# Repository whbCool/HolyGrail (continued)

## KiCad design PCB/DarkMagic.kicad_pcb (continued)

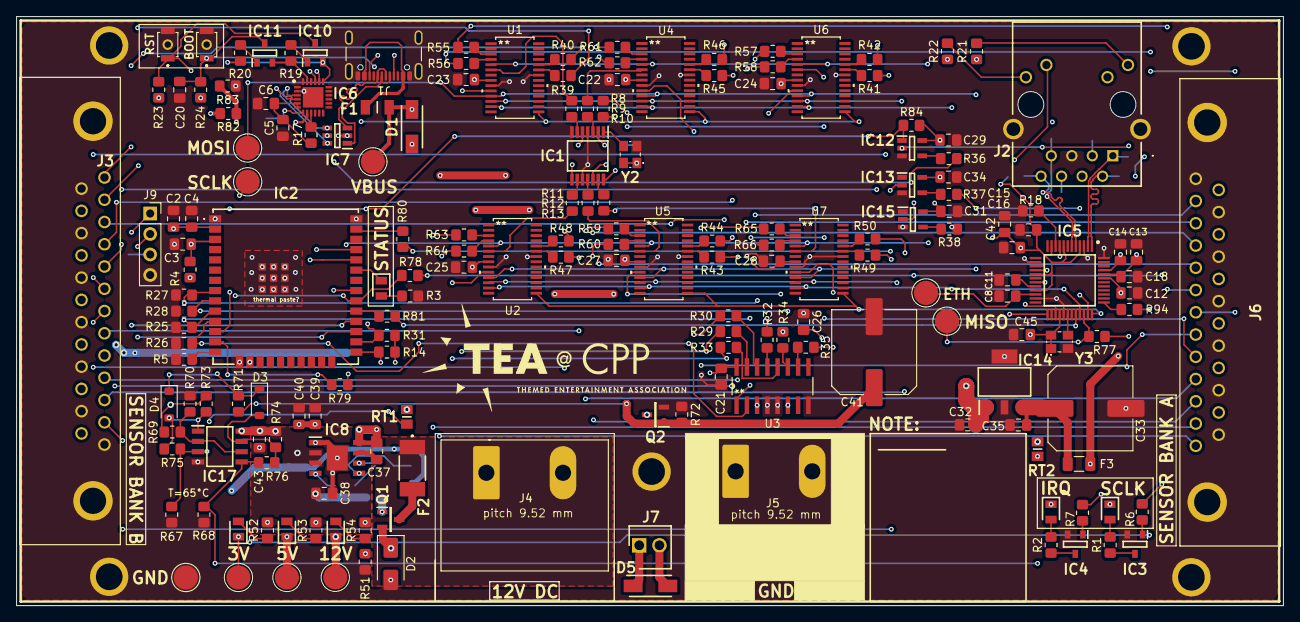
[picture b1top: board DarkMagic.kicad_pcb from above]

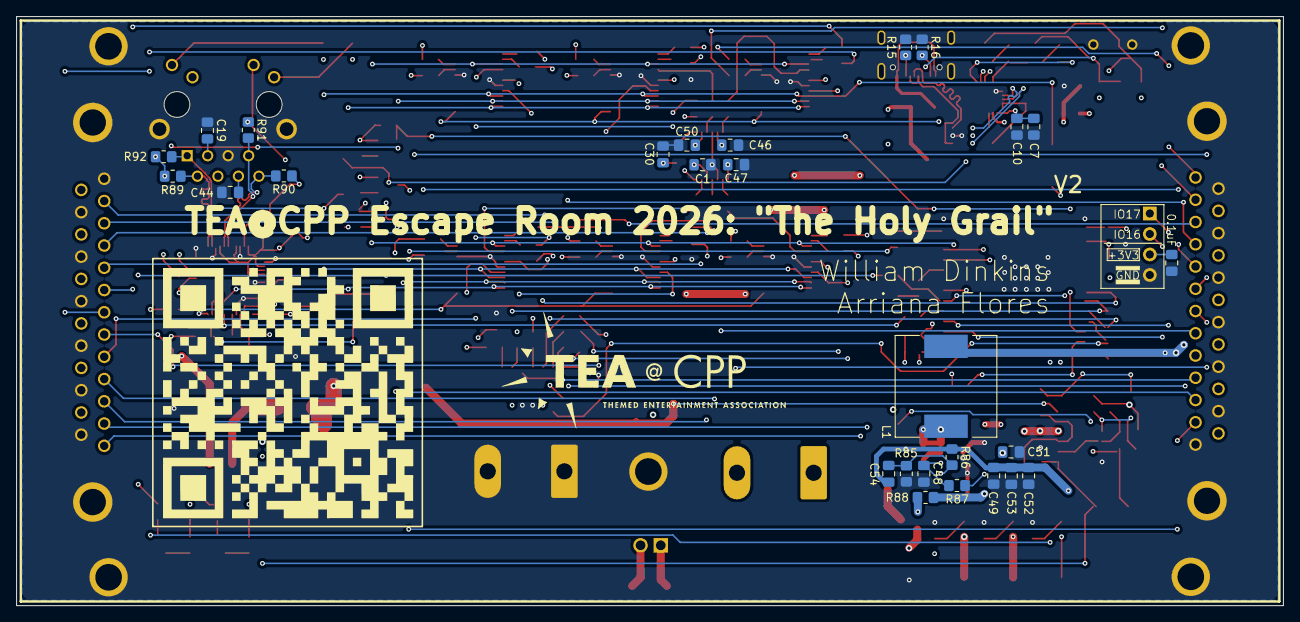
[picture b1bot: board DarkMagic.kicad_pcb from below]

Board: 6 copper layers, 157.0 x 73.0 mm, 212 parts (27 on the bottom side), 165 nets.

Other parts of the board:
C3, C4: 10uF; C_0805_2012Metric_Pad1.18x1.45mm_HandSolder
IC2: ESP32-WROOM-32UE-N16; ESP32WROOM32UEN16
IC3, IC4: MMBT3904-AQ; SOT95P240X120-3N
IRQ1: HSMN-C170; LEDC2012X90N
J9: Conn_01x04; PinSocket_1x04_P2.54mm_Vertical
R1, R2, R3: 330; R_0805_2012Metric_Pad1.20x1.40mm_HandSolder
R4, R5, R14: 10k; R_0805_2012Metric_Pad1.20x1.40mm_HandSolder
R6, R7: 4.7K; R_0805_2012Metric_Pad1.20x1.40mm_HandSolder
R8, R9, R10, R11, R12, R13: 33; R_0805_2012Metric_Pad1.20x1.40mm_HandSolder
SCLK1: HSMN-C170; LEDC2012X90N
STATUS1: HSMG-C170; LEDC2012X80N

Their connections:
/ESP_A0: IC2.10 (IO25); also elsewhere on the board
/ESP_A1: IC2.11 (IO26); also elsewhere on the board
/ESP_A2: IC2.8 (IO32); also elsewhere on the board
/ESP_E3: IC2.9 (IO33); also elsewhere on the board
/ESP_EN: C3.1, IC2.3 (EN), R4.1; also elsewhere on the board
/ESP_IO0: IC2.25 (IO0), R14.1; also elsewhere on the board
/ESP_IRQ: IC2.26 (IO4), R7.1; also elsewhere on the board
/ESP_MISO: IC2.31 (IO19); also elsewhere on the board
/ESP_MOSIT: IC2.37 (IO23); also elsewhere on the board
/ESP_RX0: IC2.34 (RXD0); also elsewhere on the board
/ESP_SCLK: R6.1; also elsewhere on the board
/ESP_SCLKT: IC2.30 (IO18); also elsewhere on the board
/ESP_SCSNT: IC2.29 (IO5); also elsewhere on the board
/ESP_TX0: IC2.35 (TXD0); also elsewhere on the board
/ESP_USRSTT: IC2.13 (IO14); also elsewhere on the board
/IO12: IC2.14 (IO12), R5.2
/IO16: IC2.27 (IO16), J9.2
/IO17: IC2.28 (IO17), J9.1
/IO21: IC2.33 (IO21), STATUS1.1 (K)
/IRQ_STAT: IC4.3 (C), R2.1
/OE: IC2.12 (IO27); also elsewhere on the board
/SCLK_STAT: IC3.3 (C), R1.1
/W5500_RST: IC2.16 (IO13); also elsewhere on the board
/XS1: R8.2; also elsewhere on the board
/XS1T: R8.1; also elsewhere on the board
/XS2: R9.2; also elsewhere on the board
/XS3: R10.2; also elsewhere on the board
/XS3T: R10.1; also elsewhere on the board
/XS4: R11.2; also elsewhere on the board
/XS4T: R11.1; also elsewhere on the board
/XS5: R12.2; also elsewhere on the board
/XS5T: R12.1; also elsewhere on the board
/XS6: R13.2; also elsewhere on the board
/XS6T: R13.1; also elsewhere on the board
unnamed: IC3.1 (B), R6.2
unnamed: IC4.1 (B), R7.2
unnamed: IRQ1.2 (A), R2.2
unnamed: R1.2, SCLK1.2 (A)
unnamed: R3.1, STATUS1.2 (A)

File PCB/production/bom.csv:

Designator,Footprint,Quantity,Value,LCSC Part #
12V1,LEDC2012X90N,1,HSMC-C170,
"3V1, STATUS1",LEDC2012X80N,2,HSMG-C170,
5V1,LEDC2012X90N,1,HSMA-C170,
"C1, C10, C12, C13, C14, C15, C16, C17, C18, C19, C2, C20, C21, C22, C23, C24, C25, C26, C27, C28, C29, C30, C31, C34, C35, C37, C42, C43, C44, C45, C46, C47, C50, C6, C8, C9",0805,36,0.1uF,
C11,0805,1,10nF,
"C3, C32, C38, C4",0805,4,10uF,
C33,C_Elec_10x10.2,1,33uF,
"C39, C40, C49, C52, C53",0805,5,22uF,
C41,C_Elec_10x10.2,1,47uF,
C48,0805,1,1uF,
"C5, C7",0805,2,4.7uF,
C51,0805,1,220nF,
C54,0805,1,39pF,
"D1, D5",DIOM5226X230N,2,B130-13-F,
D2,D_SMA,1,SMBJ26A,
"D3, D4",D_SOD-123,2,1N4148W,
F1,FUSC3216X74N,1,NANOSMDC050F_13.2-2,
F2,1812L010DR,1,1812L150_24MR,
IC1,SOP65P640X120-14N,1,5PB1106PGGI8,
"IC10, IC11, IC3, IC4",SOT95P240X120-3N,4,MMBT3904-AQ,
"IC12, IC13, IC15",SOT95P280X145-5N,3,SN74LVC1G125DBVT,
IC14,SOT230P700X180-4N,1,LM3940IMP-3.3_NOPB,
IC17,SOIC127P600X175-8N,1,LM393DR,
IC2,ESP32WROOM32UEN16,1,ESP32-WROOM-32UE-N16,
IC5,QFP50P900X900X160-48N,1,W5500,
IC6,QFN50P400X400X80-25N-D,1,CP2102N-A02-GQFN24,
IC7,SOT95P280X145-6N,1,USBLC6-2SC6,
IC8,SOIC127P600X170-9N,1,LMR33640ADDAR,
"IRQ1, SCLK1",LEDC2012X90N,2,HSMN-C170,
J1,USB_C_Receptacle_GCT_USB4105-xx-A_16P_TopMnt_Horizontal,1,USB_C_Receptacle_USB2.0_16P,
J2,TMJ0026ABNL,1,TMJ0026ABNL,
"J3, J6",57478422,2,5747842-2,
J7,SHDR2W69P0X250_1X2_500X530X1040P,1,171825-2,
L1,L_12x12mm_H4.5mm,1,7447715003,
Q1,SOT95P237X112-3N,1,SQ2319ADS-T1_BE3,
Q2,SOT95P237X112-3N,1,SQ2348ES-T1_BE3,
"R1, R2, R21, R22, R3",0805,5,330,
"R10, R11, R12, R13, R29, R30, R32, R33, R34, R35, R36, R37, R38, R39, R40, R41, R42, R43, R44, R45, R46, R47, R48, R49, R50, R55, R56, R57, R58, R59, R60, R61, R62, R63, R64, R65, R66, R77, R78, R79, R8, R80, R81, R9",0805,44,33,
"R14, R17, R19, R20, R23, R24, R25, R26, R27, R28, R4, R5, R51, R69, R70, R71, R72, R73, R74, R84, R88, R93",0805,22,10k,
"R15, R16",0805,2,5.1k,
R18,0805,1,12.4k,
"R31, R54, R6, R7",0805,4,4.7k,
R52,0805,1,680,
R53,0805,1,1.5k,
"R67, R68",0805,2,2.55K,
"R75, R76",0805,2,1M,
R82,0805,1,22.1k,
R83,0805,1,47.5k,
R85,0805,1,24.9k,
"R86, R87",0805,2,100k,
"R89, R90, R91, R92",0805,4,49.9,
"RT1, RT2",THRMC2012X130N,2,B57442V5103J062,
"S1, S2",B3U1000PB,2,B3U-1000P-B,
"U1, U2, U4, U5, U6, U7",TSSOP28_SOT361-1_NXP,6,SC16IS752IPW_128,
U3,D16,1,CD74HC138QM96Q1,
Y2,ASE24576MHZLCT,1,ASE-14.7456MHZ-LC-T,
Y3,ASE24576MHZLCT,1,ASE-25.000MHZ-LC-T,

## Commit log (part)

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2026-05-25 Add ESP-IDF devcontainer and project scaffold
    Initial scaffold for an ESP-IDF project: adds a devcontainer (Dockerfile + devcontainer.json) using espressif/idf, installs udev, and sources the ESP-IDF environment. Includes VS Code configs (c_cpp_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
2026-05-25 feat: initialize project with main application entry point and system info logging
2026-05-25 feat: initialize LD2410C radar sensor integration and target tracking application
2026-05-25 Add project title to README
2026-05-25 Altered settings.json
2026-05-25 docs: add project documentation and schematic reference for The Holy Grail PCB
2026-05-26 feat: implement W5500 Ethernet driver and MQTT client for HolyGrail radar data aggregation
2026-05-26 cleaned warnings
2026-05-26 cleaned more warnings
2026-05-26 Update DarkMagic.pdf
    Updated schematic
2026-05-26 Formatting
2026-05-26 Edited description
2026-05-26 docs: format major components list as a bulleted list in README
2026-05-26 PCB Layout
    Uploaded the KiCad project here
2026-05-26 File organizing
2026-05-26 Update README with image and PCB details
    Added an image and expanded the description of the Holy Grail PCB.
2026-05-26 More formatting
2026-05-26 Revise design requirements in README.md
    Updated design requirements for clarity and conciseness.
2026-05-26 Update README to include walkthrough.md reference
    Added a reference to the walkthrough document for more details.
2026-05-26 Revise README for clarity and conciseness
    Updated the README to clarify project details and remove redundancy.
2026-05-26 Update DarkMagic PCB and add production files
    Clean up and adjust DarkMagic.kicad_pcb geometry (remove stray segments, tweak segment endpoints and UUIDs, and refine track/polyline coordinates). Add production outputs and artifacts for manufactur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
2026-05-26 Ignore DarkMagic backups and remove zip
2026-05-26 git ignore edits
2026-05-26 Capacitor placement
    Moved some decoupling caps from the top to the bottom. Also, file organization
2026-05-26 Wiring
    Tweaked wiring
2026-05-26 Update README to specify USB port for debugging
2026-05-26 Add footprints & datasheets; clean PCB file
    Add numerous component datasheets to PCB/Datasheets and introduce new footprints (DarkMagic:SRN2010BTA3R3M and DarkMagic:1812L010DR). Remove many redundant KiLib_Generator properties and perform foot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
2026-05-27 Revise PCB footprints, nets and metadata
    Refactor multiple footprints and metadata across the DarkMagic PCB files. Removed an obsolete SRN2010 inductor footprint and replaced a capacitor footprint with Inductor_SMD:L_12x12mm_H4.5mm (L1). St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
2026-05-27 Revise README with new image and components
    Updated image reference and component list in README.
2026-05-27 Silkscreen to 12V and major PCB reroute
    Update silkscreen and documentation from 24V to 12V (text and warning box) and adjust a small graphic line position. Perform extensive PCB rework: replace and reassign many segments/vias, add new net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
2026-05-27 Update BOM parts and adjust schematics text/layout
    Apply multiple BOM updates and schematic edits: replace/update capacitor, diode, TVS, fuse, regulator, transistor, connector and resistor part numbers and quantities in DarkMagic.csv; add new compone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
2026-05-27 Update PCB layout, BOM and production files
    Multiple PCB and production updates: adjust component reference positions/rotations and silkscreen stroke widths; clear zone_layer_connections entries; add/remove vias and modify several copper segme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
2026-05-28 PCB Layout optimizations
2026-05-28 KiCad: adjust PCB coords, routing & schematic
    Minor PCB and schematic tweaks: update resistor and via Y coordinates in DarkMagic.kicad_pcb, adjust F.Cu routing segments (added one segment, changed segment endpoints and UUIDs) to clean up trace g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
2026-05-28 Add 1x04 pin socket and clean footprint attrs
    Inserted a new 1x04 vertical pin socket footprint (J9) for the ESP32 connector and added corresponding silk labels for IO pins. Removed stray "dnp" attributes from multiple footprint pad definitions 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
2026-05-29 Move R15/R16 to bottom side and clean generated files
    Replace front-side R15/R16 footprints with mirrored bottom-side footprints (moved from F.Cu to B.Cu), updating silk/fab text mirroring and pad layers. Remove duplicate front-side footprint entries. D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
2026-05-30 Add bottom hand-solder caps and update BOM
    Update PCB to add bottom-side hand-solder 0805 capacitor footprints and sync BOM. DarkMagic.csv: increment 0.1uF part count (34→35) and 4.7uF count (1→2) and update component lists. DarkMagic.kicad_p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
2026-05-31 Add four 49.9Ω resistors and update PCB
    Add R89–R92 as 49.9Ω SMD 0805 hand-solder footprints and corresponding BOM entries. Update PCB layout with new footprints, vias and copper segments to connect the parts into +3V3 and related signal n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
2026-05-31 Adjust PCB spline vertex coordinates
    Tweak several (xy ...) control points in PCB/DarkMagic.kicad_pcb to correct and smooth spline/outline geometry. The changes are minor coordinate adjustments to refine the board outline and rendering;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
2026-06-01 PCB: change mask color, pad & routing fixes
    Update PCB and project files: DarkMagic.kicad_pcb had solder mask color changed from Black to Green, multiple pad definitions converted from np_thru_hole to thru_hole (add remove_unused_layers where 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
2026-06-05 Connect GND zones to In2.Cu layer
    Add In2.Cu to multiple zone_layer_connections for GND zones in DarkMagic.kicad_pcb so ground pours can use the inner layer. Also update several F.Cu filled_polygon shapes (polygon geometry replaced/s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
2026-06-21 PCB: Reroute nets and update component value
    Modify DarkMagic.kicad_pcb to correct power routing and update a component value. Changes include: changed a component Value from "CDCLVC1106PWR" to "5PB1106PGGI8", reassigned a pad/net from GND to +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
2026-06-22 Add 0805 handsolder footprint and reroute nets
    Add an 0805 hand-solder capacitor footprint (Pad1.18x1.45mm) on B.Cu (C50) and update existing 0805 footprint reference placement. Add copper segments and a via to connect +3V3 and GND between F.Cu a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
2026-06-27 V2 Polishing
    Minor layout optimizations, including removed vias and rerouted power rails
2026-06-28 feat: initialize project with ESP32 schematic, ethernet port layout, and base firmware.
